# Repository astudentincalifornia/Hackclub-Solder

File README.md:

# No Fear Linux, the ram eater
Did Linux eat your RAM again?! A simple double SR Latch circuit connected to the same reset acts as a simple 2-bit memory. It is controlled by two buttons and reset by one.

## Features
1. Can run LLMs*
2. Vibration
3. Idk why it would ever be needed
<br>
*you would need over 128000000000 of this item and need to make necessary modifications

## BOM
<br>1 Battery Holder
<br>4 LEDs
<br>1 Motor_DC
<br>6 NPN 2N3904 Transistors
<br>17 Resistors (220 Ohms)
<br>3 Push Switches

## Schematic

## PCB 3D Front and Back

## PCB

---
Made by '@ilikebananas' as a part of http://solder.hackclub.com/!
<br>
Bananas,
<br>
Yilin Z.

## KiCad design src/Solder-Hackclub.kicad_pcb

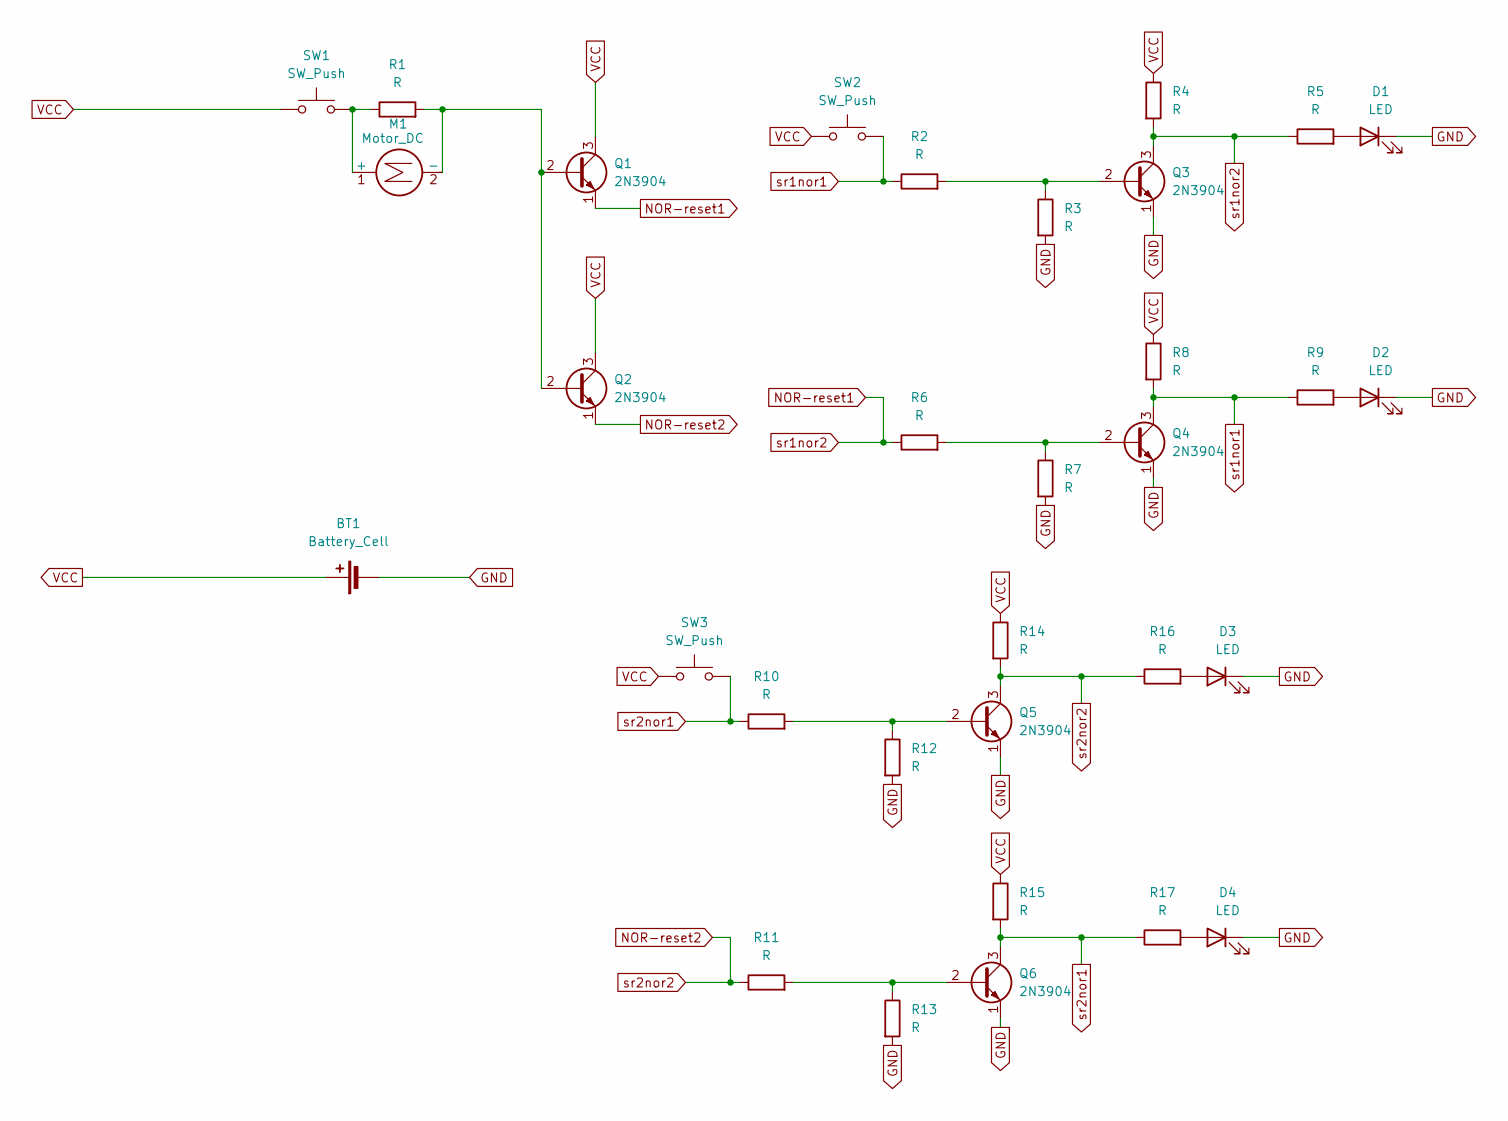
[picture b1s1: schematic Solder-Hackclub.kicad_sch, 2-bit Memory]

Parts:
BT1: Battery_Cell; BatteryHolder_Keystone_3034_1x20mm
D1, D2, D3, D4: LED; LED_D5.0mm
M1: Motor_DC; PinHeader_1x02_P2.54mm_Vertical
Q1, Q2, Q3, Q4, Q5, Q6: 2N3904; TO-92_Inline
R1, R2, R3, R4, R5, R6, R7, R8, R9, R10, R11, R12, R13, R14, R15, R16, R17: R; R_Axial_DIN0207_L6.3mm_D2.5mm_P7.62mm_Horizontal
SW1, SW2, SW3: SW_Push; SW_PUSH_6mm

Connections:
GND: BT1.2 (-), D1.1 (K), D2.1 (K), D3.1 (K), D4.1 (K), Q3.1 (E), Q4.1 (E), Q5.1 (E), Q6.1 (E), R3.2, R7.2, R12.2, R13.2
NOR-reset1: Q1.1 (E), Q3.3 (C), R4.2, R5.1, R6.1
NOR-reset2: Q2.1 (E), Q5.3 (C), R11.1, R14.2, R16.1
unnamed: D1.2 (A), R5.2
unnamed: D2.2 (A), R9.2
unnamed: D3.2 (A), R16.2
unnamed: D4.2 (A), R17.2
unnamed: M1.1 (+), R1.1, SW1.2
unnamed: M1.2 (-), Q1.2 (B), Q2.2 (B), R1.2
unnamed: Q3.2 (B), R2.2, R3.1
unnamed: Q4.2 (B), R6.2, R7.1
unnamed: Q5.2 (B), R10.2, R12.1
unnamed: Q6.2 (B), R11.2, R13.1
VCC: BT1.1 (+), Q1.3 (C), Q2.3 (C), R4.1, R8.1, R14.1, R15.1, SW1.1, SW2.1, SW3.1
sr1nor1: Q4.3 (C), R2.1, R8.2, R9.1, SW2.2
sr2nor1: Q6.3 (C), R10.1, R15.2, R17.1, SW3.2

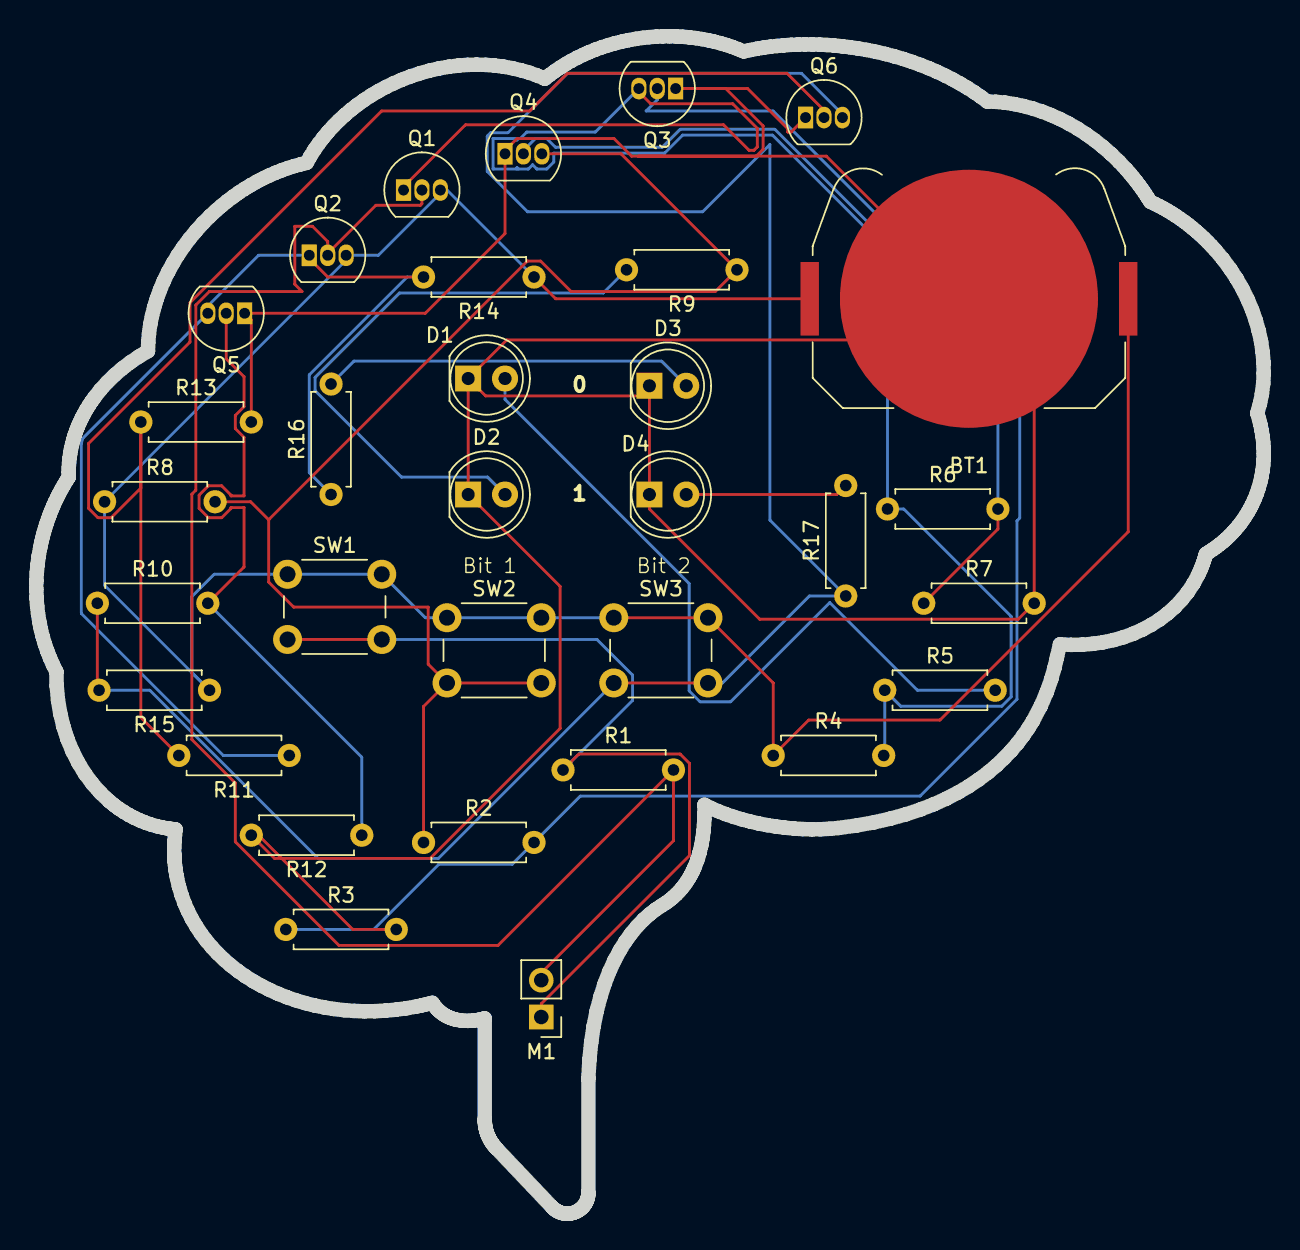
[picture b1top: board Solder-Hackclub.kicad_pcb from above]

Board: 2 copper layers, 84.7 x 81.2 mm, 32 parts (0 on the bottom side), 16 nets.

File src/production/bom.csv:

Designator,Footprint,Quantity,Value,LCSC Part #
BT1,BatteryHolder_Keystone_3034_1x20mm,1,Battery_Cell,
"D1, D2, D3, D4",LED_D5.0mm,4,LED,
M1,PinHeader_1x02_P2.54mm_Vertical,1,Motor_DC,
"Q1, Q2, Q3, Q4, Q5, Q6",TO-92_Inline,6,2N3904,
"R1, R10, R11, R12, R13, R14, R15, R16, R17, R2, R3, R4, R5, R6, R7, R8, R9",R_Axial_DIN0207_L6.3mm_D2.5mm_P7.62mm_Horizontal,17,R,
"SW1, SW2, SW3",SW_PUSH_6mm,3,SW_Push,

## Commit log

2025-05-27 Create yes
